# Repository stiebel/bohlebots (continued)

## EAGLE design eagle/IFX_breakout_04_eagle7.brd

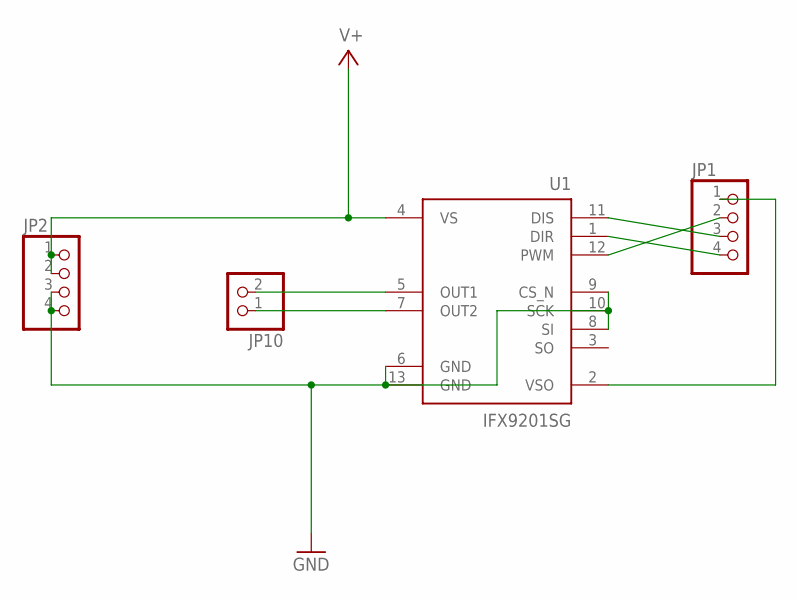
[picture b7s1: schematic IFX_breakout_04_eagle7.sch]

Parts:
JP1, JP2: PINHD-1X4; 1X04
JP10: PINHD-1X2/90; 1X02/90
U1: IFX9201SG; SOP100P1030X260-13N

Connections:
!ENA: JP1.3, U1.11 (DIS)
DIR: JP1.4, U1.1 (DIR)
GND: JP2.3, JP2.4, U1.6 (GND), U1.8 (SI), U1.9 (CS_N), U1.10 (SCK), U1.13 (GND)
unnamed: JP10.2, U1.5 (OUT1)
unnamed: JP10.1, U1.7 (OUT2)
PWM: JP1.2, U1.12 (PWM)
V3.3: JP1.1, U1.2 (VSO)
V+: JP2.1, JP2.2, U1.4 (VS)

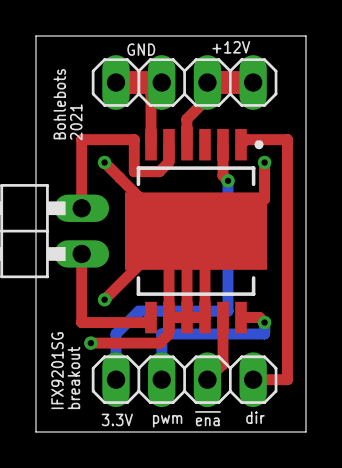
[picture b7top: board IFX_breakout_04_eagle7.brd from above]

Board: 2 copper layers, 15.0 x 22.0 mm, 4 parts (0 on the bottom side), 8 nets.

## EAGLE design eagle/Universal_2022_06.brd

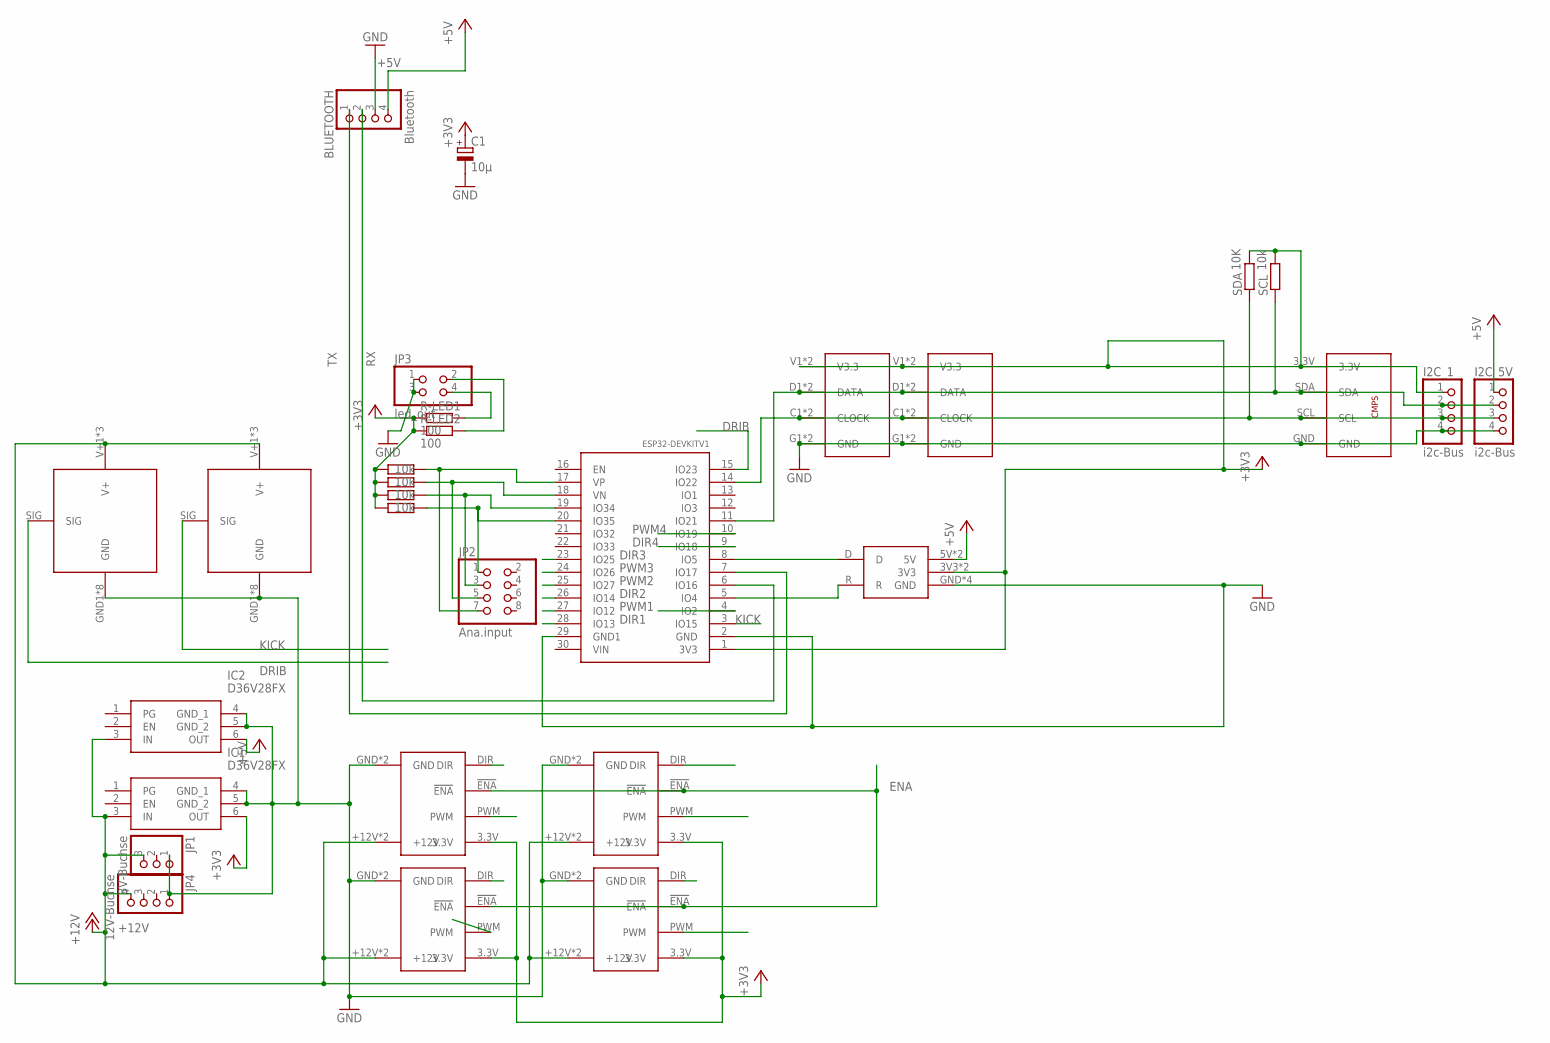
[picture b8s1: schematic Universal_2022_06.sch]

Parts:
BLUETOOTH: Bluetooth; 1X04/90
C1: 10µ; E2,5-6E
I2C_1, I2C_5V: i2c-Bus; 1X04
IC1, IC2: D36V28FX
JP1: 8V-Buchse; 1X03
JP2: Ana.input; 2X04
JP3: led_out; 2X02
JP4: 12V-Buchse; 1X04
R-LED1, R-LED2: 100; 0207/10
R_AD14, R_AD25, R_AD26, R_AD27: 10k; 0207/10
SCL: 10k; 0207/10
SDA: 10K; 0207/10
U$1, U$3: TASTER_LED
U$5: CANBUS
U$7, U$17: KICKER
U$8: CMPS
U$11, U$14, U$15, U$16: IFX9201BREAKOUT
U$13: ESP32DEVKITV1; ESP32-DEVKITV1

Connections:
+3V3: C1.+, I2C_1.1, IC1.6 (OUT), R-LED1.1, R-LED2.1, R_AD14.1, R_AD25.1, R_AD26.1, R_AD27.1, SCL.2, SDA.2, U$1.V1 (V3.3), U$1.V2 (V3.3), U$3.V1 (V3.3), U$3.V2 (V3.3), U$5.3V3, U$5.3V3_1 (3V3), U$8.3.3V, U$11.3.3V, U$13.1 (3V3), U$14.3.3V, U$15.3.3V, U$16.3.3V
+5V: BLUETOOTH.4, I2C_5V.1, IC2.6 (OUT), U$5.5V, U$5.5V_1 (5V)
+12V: IC1.3 (IN), IC2.3 (IN), JP1.3, JP4.4, U$7.V+1 (V+), U$7.V+2 (V+), U$7.V+3 (V+), U$11.+12V, U$11.+12V2 (+12V), U$14.+12V, U$14.+12V2 (+12V), U$15.+12V, U$15.+12V2 (+12V), U$16.+12V, U$16.+12V2 (+12V), U$17.V+1 (V+), U$17.V+2 (V+), U$17.V+3 (V+)
CLOCK: I2C_1.3, I2C_5V.3, SDA.1, U$1.C1 (CLOCK), U$1.C2 (CLOCK), U$3.C1 (CLOCK), U$3.C2 (CLOCK), U$8.SCL, U$13.14 (IO22)
D: U$5.D, U$13.8 (IO5)
DATA: I2C_1.2, I2C_5V.2, SCL.1, U$1.D1 (DATA), U$1.D2 (DATA), U$3.D1 (DATA), U$3.D2 (DATA), U$8.SDA, U$13.11 (IO21)
DIR1: U$13.28 (IO13), U$16.DIR
DIR2: U$13.26 (IO14), U$15.DIR
DIR3: U$11.DIR, U$13.23 (IO25)
DIR4: U$13.9 (IO18), U$14.DIR
DRIB: U$7.SIG, U$13.15 (IO23)
ENA: U$11.!ENA, U$13.4 (IO2), U$14.!ENA, U$15.!ENA, U$16.!ENA
GND: BLUETOOTH.3, C1.-, I2C_1.4, I2C_5V.4, IC1.4 (GND_1), IC1.5 (GND_2), IC2.4 (GND_1), IC2.5 (GND_2), JP1.1, JP3.1, JP3.3, JP4.1, U$1.G1 (GND), U$1.G2 (GND), U$3.G1 (GND), U$3.G2 (GND), U$5.GND, U$5.GND_1 (GND), U$5.GND_2 (GND), U$5.GND_3 (GND), U$7.GND1 (GND), U$7.GND2 (GND), U$7.GND3 (GND), U$7.GND4 (GND), U$7.GND5 (GND), U$7.GND6 (GND), U$7.GND7 (GND), U$7.GND8 (GND), U$8.GND, U$11.GND, U$11.GND2 (GND), U$13.2 (GND), U$13.29 (GND1), U$14.GND, U$14.GND2 (GND), U$15.GND, U$15.GND2 (GND), U$16.GND, U$16.GND2 (GND), U$17.GND1 (GND), U$17.GND2 (GND), U$17.GND3 (GND), U$17.GND4 (GND), U$17.GND5 (GND), U$17.GND6 (GND), U$17.GND7 (GND), U$17.GND8 (GND)
KICK: U$13.3 (IO15), U$17.SIG
unnamed: JP2.7, R_AD25.2, U$13.17 (VP)
unnamed: JP2.5, R_AD26.2, U$13.18 (VN)
unnamed: JP2.3, R_AD27.2, U$13.19 (IO34)
unnamed: JP2.1, R_AD14.2, U$13.20 (IO35)
unnamed: JP3.4, R-LED1.2
unnamed: JP3.2, R-LED2.2
PWM1: U$13.27 (IO12), U$16.PWM
PWM2: U$13.25 (IO27), U$15.PWM
PWM3: U$11.PWM, U$13.24 (IO26)
PWM4: U$13.10 (IO19), U$14.PWM
R: U$5.R, U$13.5 (IO4)
RX: BLUETOOTH.2, U$13.6 (IO16)
TX: BLUETOOTH.1, U$13.7 (IO17)

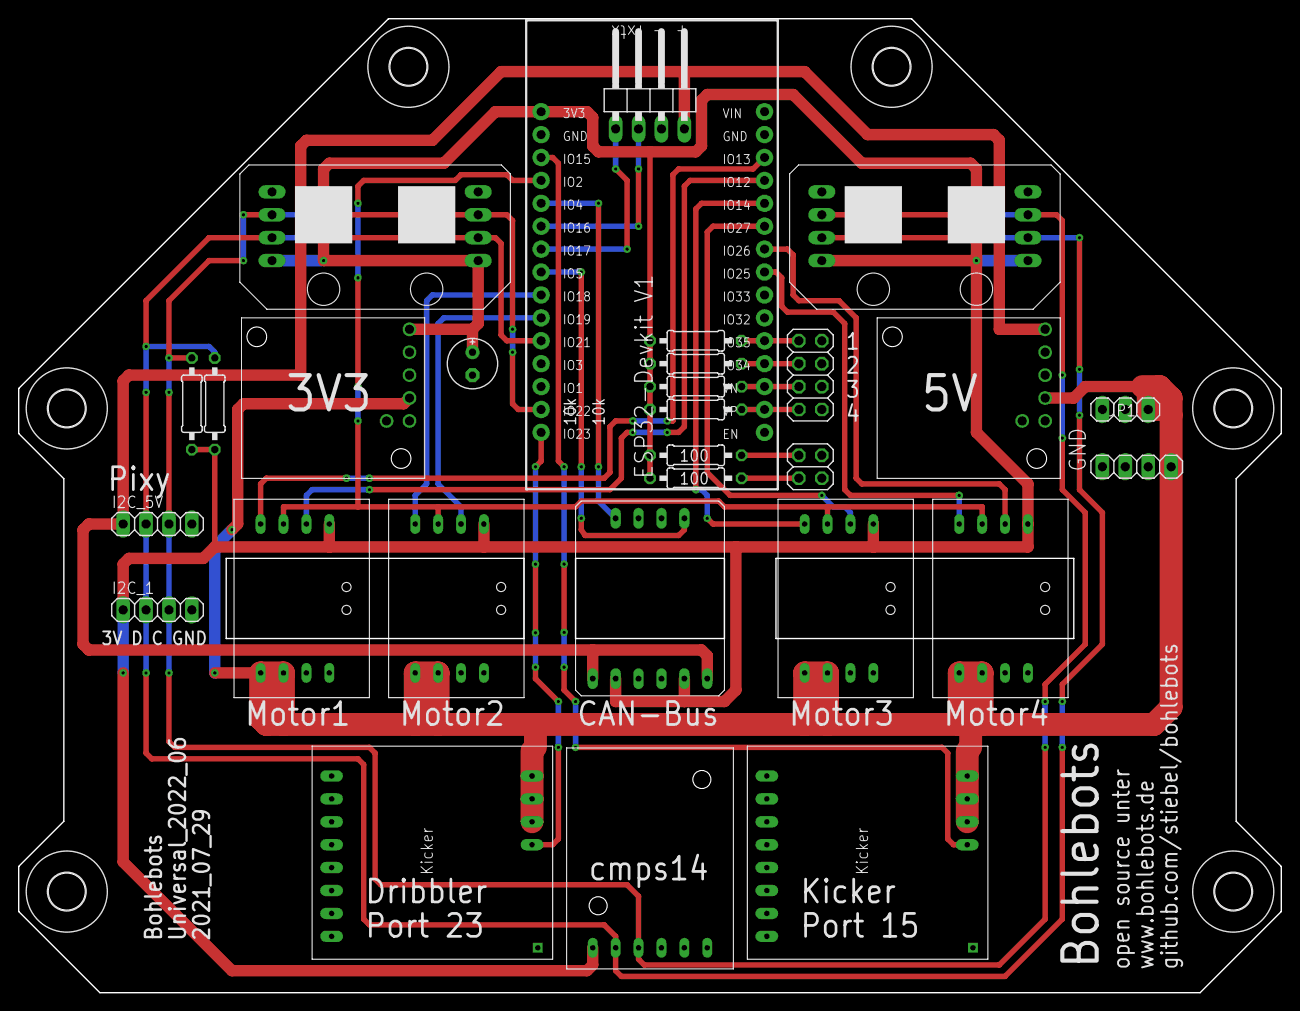
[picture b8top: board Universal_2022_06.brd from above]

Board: 2 copper layers, 140.0 x 108.0 mm, 35 parts (0 on the bottom side), 27 nets.

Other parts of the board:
U$2, U$4, U$6, U$9, U$10, U$12: 4,1

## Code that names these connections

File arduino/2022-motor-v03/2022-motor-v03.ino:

#include "functions.h"

void setup() 
{
  Serial.begin(115200);
  Serial.print("Setup ... ");
  Serial.println("abs="+String(myAbs(-0.5)));
  
  // Motor Pins einrichten
  ledcAttachPin(PWM1, 1); ledcSetup(1, 1000, 8);  ledcWrite(1, 0);
  ledcAttachPin(PWM2, 2); ledcSetup(2, 1000, 8);  ledcWrite(2, 0);
  ledcAttachPin(PWM3, 3); ledcSetup(3, 1000, 8);  ledcWrite(3, 0);
  ledcAttachPin(PWM4, 4); ledcSetup(4, 1000, 8);  ledcWrite(4, 0);
   
  pinMode(ENA, OUTPUT);  digitalWrite(ENA, LOW);
  pinMode(DIR1, OUTPUT); 
  pinMode(DIR2, OUTPUT);
  pinMode(DIR3, OUTPUT);
  pinMode(DIR4, OUTPUT);

  pinMode(LED, OUTPUT);
  
 
  while (!Serial);

  Serial.println("CAN Setup");

  // start the CAN bus at 500 kbps
  if (!CAN.begin(500E3)) 
  {
    Serial.println("Starting CAN failed!");
    while (1);
  }
   CAN.filter(0x10);
   Serial.print("Setup beendet");

   fahre(0,0,0);
 
  delay(500);
  
}
void loop() 
{  

  //fahre(0,0,20);
  
  //roll();
   
   
   if (startzeit<20)   startzeit++;
   checkCanBus(); 
   if (timeout>100) roll();
  delay(1);
  Serial.println(startzeit);
}

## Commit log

2020-11-06 Update LICENSE
2021-11-27 Rename Kick_mess_01.brd to Measurment_device/Kick_mess_01.brd
2021-11-27 Rename Kick_mess_01.sch to Measurement_device/Kick_mess_01.sch
2022-07-01 Create quadro
2024-11-17 Mit Colab erstellt
